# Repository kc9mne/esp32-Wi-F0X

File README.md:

# Wi-F0X

**A phone-configured 2 m fox-hunt beacon for the LilyGO T-Beam Supreme 144-148 MHz.**
By Paul Gariepy, KC9MNE — [kc9mne.com](https://kc9mne.com)

Wi-F0X turns a stock T-Beam Supreme (ESP32-S3 + SX1278, 2 m version) into a fox for
transmitter hunts and ARDF. You set it up from a phone over its own Wi-Fi: no PC, no
programming cable, no app. It has been used at a real hunt alongside Byonics MicroFox 50s.

### Demo

https://github.com/user-attachments/assets/96026c00-8a75-42aa-9971-1123c974c956

The prototype on the bench sending a voice clip and tracking tones, received on a handheld.
[Watch on YouTube](https://youtu.be/PTlThZ83Uh0) (41 s), or
[download the MP4](https://github.com/kc9mne/esp32-Wi-F0X/raw/main/media/wi-f0x-demo-720p.mp4) (8 MB).

## Features

- **Beacon cycle:** tracking tone, optional Morse message, then `DE <call> FOX <n>` in CW.
- **Tracking modes:** steady tone, warble, repeating ARDF MO pattern (MOE, MOI, MOS, MOH,
  MO5 for fox 1-5), and a **MicroFox 50 sequence** mode that matches the MF-50's tones and
  timing so Wi-F0X can join an existing MF-50 rotation.
- **Voice clips:** upload audio from the phone (converted in the browser to 8 kHz mono WAV)
  and play one clip per cycle, true FM. Good for jokes, taunts, or announcements.
- **Phone control page:** frequency, power, tone length, interval, start delay, run limit,
  pitch, Morse speed, auto start, and start/stop/test buttons.
- **OLED status:** a KC9MNE Wi-F0X boot screen, then fox ID and call, frequency and power, beacon state with countdown,
  battery percent and estimated runtime, Wi-Fi name and password, and a Wi-Fi QR code.
- **Settings survive power-off** (stored in the ESP32's flash).
- **Power:** 2-10 dBm selectable. The CPU idles at 80 MHz and only steps up for voice.

## Hardware

- LilyGO **T-Beam Supreme, 144-148 MHz** version (SX1278). The 433/868/915 MHz versions
  will not work on 2 m.
- An 18650 cell (tested with a Samsung INR18650-35E).
- A 2 m antenna on the SMA. **Never transmit without an antenna.**
- Optional: a microSD card (FAT32) for voice clips.

### Enclosure

A clear tube with rubber end caps makes a see-through, water-resistant fox: you can read the
OLED without opening it, and the antenna comes out through one cap.

- **Tube:** [MECCANIXITY rigid clear polycarbonate tube](https://www.amazon.com/dp/B0BKQCXM6C),
  1.5 in (37.6 mm) ID, 1.6 in (40 mm) OD, 9.6 in (245 mm) long. One tube is enough for two foxes.
- **End caps:** [standard 1.5 in rubber end caps](https://www.amazon.com/dp/B07RGMFH9F), two per fox.

Cut the tube in half (about 4.8 in each) so the T-Beam (with its 18650) slides in, fit a cap on each end, and
pass the antenna through a hole in one cap. Pull a cap off to reach the power switch.

## Build and flash

Install [PlatformIO](https://platformio.org/), plug the T-Beam in over USB-C, then:

```bash
pio run -t upload
```

The first upload may need download mode: hold BOOT, tap RESET, release BOOT. After that
the firmware can put itself into download mode: send `b` over the USB serial port at
115200 baud, upload, then clear the force-download flag so it boots normally:

```bash
esptool.py --before no_reset --after hard_reset write_mem 0x6000812C 0 0xFFFFFFFF
```

Other serial commands: `t` sends one test cycle, `r` restarts, `h` runs a web self-test.

## Using it

1. Power on. The OLED shows the Wi-F0X boot screen, then the status screen.
2. Wi-Fi is on for 5 minutes after boot. Press **BOOT** to turn it on again later.
   Until a phone joins, the OLED alternates between the status screen and a **QR code**:
   point your phone camera at it to join the fox's network. The network name (`FOX-xxxx`)
   and password are shown beside the code for typing in by hand. Each fox makes its own
   random password on first boot (two letters and six digits, e.g. `kc482913`) and keeps it.
3. Open `http://192.168.4.1` on the phone.
4. Open **Settings**, enter **your callsign**, fox number, frequency and timing, and save.
   The callsign starts as the placeholder `F0X-01`: change it to yours before you transmit.
5. Press **Test** to send one cycle, then **Start**. With a start delay set, the fox waits
   before its first transmission (handy for MF-50-style sequencing).
6. For voice, open **Audio** and upload clips from your phone.

## How the audio works

- **Tones and Morse** use RadioLib's `AFSKClient`, toggling the SX1278's DIO2 data pin while
  the radio is in direct FSK transmit mode.
- **Voice** is true FM done in software: the SX1278's FastHop mode lets the frequency change
  while transmitting, so the ESP32 writes a new carrier frequency over SPI 8,000 times a
  second, offset by each audio sample (up to ±4 kHz, in 61 Hz steps). A second task reads
  the SD card into a double buffer so the card never interrupts the audio. See `playClip()`
  in `src/main.cpp`.

## Rules and safety

- You need an amateur radio licence to transmit on 2 m, and the fox must identify with
  **your** callsign. Wi-F0X sends the CW ID every cycle.
- Power is capped at 10 dBm in the firmware. The T-Beam's harmonics have not been measured;
  check yours with a spectrum analyser or service monitor before raising power or running
  long hunts.
- US rules don't allow LoRa on 2 m; Wi-F0X uses only FM/FSK tones and voice.

## Custom board (experimental)

`hardware/` holds a dedicated, smaller Wi-F0X board in KiCad 9: ESP32-S3, SX1278 at
+14 dBm, TP4056 charger and an 18650 on the back, sized to fit a 37.6 mm clear tube. It is
fully routed with JLCPCB order files, but **has not been built or tested**, and at small
quantities it costs more than a T-Beam. See [hardware/README.md](hardware/README.md).

## License

MIT — see [LICENSE](LICENSE). If you build on Wi-F0X, please keep the credit to KC9MNE.

73 de KC9MNE

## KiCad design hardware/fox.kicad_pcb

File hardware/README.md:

# 2 m fox board: ESP32-S3 + SX1278

A dedicated board to replace the T-Beam Supreme: same firmware features (phone setup over
Wi-Fi, SD voice clips, MO patterns, Morse ID), 25 mW on 144–148 MHz, one 18650 cell,
target cost about $20 assembled at JLCPCB.

## Files

| File | What it is |
|---|---|
| `gen_schematic.py` | **Source of truth.** Every part and every connection. Edit this, then rerun it. |
| `fox.kicad_sch` | Generated schematic. Parts are connected by net labels on each pin, not drawn wires. |
| `fox.kicad_sym`, `sym-lib-table` | TP4056, FS8205A and TCXO symbols, which the stock KiCad libraries lack. |
| `fox.pdf`, `fox.net` | Exported schematic and netlist. |
| `fox_bom_jlc.csv` | JLCPCB assembly BOM (Comment, Designator, Footprint, LCSC Part #), one row per LCSC number. The OLED header J3 and the edge SMA J2 (C496550, clamps both sides of the edge) are left off and soldered by hand. |
| `check_netlist.py` | Confirms KiCad's netlist matches the script, pin by pin. |
| `rf_calc.py` | Matching-network and low-pass filter calculations quoted below. |
| `gen_board.py`, `autoroute.py`, `fox.kicad_pcb` | Board generator and router (KiCad's Python), and the routed board. |
| `silk.py` | Places reference labels clear of pads, vias and each other (autoroute.py runs it). |
| `fix_footprints.py`, `lib/`, `fp-lib-table` | LCSC footprints and 3D models, pads fixed to match the schematic. |
| `renders/` | 3D renders of the board. |
| `sexp.py` | Small KiCad file reader/writer used by the scripts. |

Regenerate and check:

```
python gen_schematic.py
kicad-cli sch erc fox.kicad_sch
kicad-cli sch export netlist --format kicadsexpr -o fox.net fox.kicad_sch
python check_netlist.py
```

Current state: ERC 0 violations; netlist check 83 nets, 265 pins, 0 problems.

## Blocks

**Power.** USB-C (5.1 k CC pull-downs, USBLC6 ESD) feeds a TP4056 charging the cell at
500 mA (R3 = 2.4 k). DW01A + FS8205A protect the unprotected Samsung 35E against
over-discharge (about 2.4 V), overcharge and short circuit. The slide switch sits after the
charger, so the cell charges with the fox switched off. An ME6211 LDO makes 3.3 V.
Below about 3.4 V the 3.3 V rail starts to sag; the firmware already stops transmitting at
3.3 V.

**Sensing.** VSYS/2 on GPIO 6 for battery voltage (replaces the AXP2101 readings).
VBUS/2 on GPIO 16 to tell when USB is plugged in. Charge state is on the red/green LEDs.

**ESP32-S3-WROOM-1-N8.** Radio, SD and OLED use the same GPIOs as the T-Beam Supreme, so
those parts of the firmware carry over unchanged:

| Function | GPIO |
|---|---|
| Radio SCK / MISO / MOSI / NSS | 12 / 13 / 11 / 10 |
| Radio RESET / DIO0 / DIO1 / DIO2 | 5 / 2 / 1 / 4 |
| SD SCK / MISO / MOSI / CS | 36 / 37 / 35 / 47 |
| OLED SDA / SCL | 17 / 18 |
| Battery sense / USB sense / status LED | 6 / 16 / 7 |
| BOOT button | 0 |

GPIO 35–37 are free only because the N8 module has no octal PSRAM; don't substitute an
N8R8 or N16R8 module.

**Radio.** SX1278 with an Epson TG2520SMN 32 MHz clipped-sine TCXO (±0.5 ppm, about
±75 Hz at 146 MHz) AC-coupled into XTA through 10 nF, XTB open. TCXO pin 1 is grounded:
Epson says it must be open or grounded. The firmware must set `RegTcxo` (0x4B) bit 4
before starting the radio, and switch output from PA_BOOST to the RFO pin.

**OLED firmware change.** The T-Beam has a 1.3 in SH1106; 0.96 in modules are usually
SSD1306, so the U8g2 setup call changes from `sh1106` to `ssd1306` (otherwise the image
is shifted by 2 pixels). Read upright, the module's header is at the top of the image,
which here is the ESP32 end. If the fox hangs cap end up, use `U8G2_R2` to turn the image.

The FS8205A is the SOT-23-6 version (the TSSOP-8 one is out of stock). Its pinout is from
the Tech Public datasheet: 1 S1, 2 D, 3 S2, 4 G2, 5 D, 6 G1.

## RF network

Semtech AN1200.19 Figure 6, the single-path RFO_LF/RFI_LF design: transmit and receive
share one port, so no RF switch is needed. Semtech warns against combining PA_BOOST with
RFI this way, which is why output is the RFO pin at up to +14 dBm (25 mW) rather than
PA_BOOST at +17 dBm.

Every value is Semtech's 169 MHz BOM scaled by 169/146 and rounded to a standard value:

| Semtech | 169 MHz | This board | 146 MHz | Role |
|---|---|---|---|---|
| Lp | 100 nH | L1 | 120 nH | PA bias feed from VR_PA |
| Cd | 220 pF | C20 | 270 pF | VR_PA decoupling (+ C21 10 nF) |
| C1 | 15 pF | C22 | 18 pF | shunt at the RF pin |
| C10 | 5.6 pF | C23 | 6.8 pF | RX branch |
| L0 | 82 nH | L2 | 91 nH | RX branch to ground |
| L1 | 56 nH | L3 | 68 nH | series match |
| Cc | 220 pF | C24 | 270 pF | DC block |
| C2 / C3 | 33 pF | C25 / C26 | 39 pF | low-pass |
| L2 | 47 nH | L4 | 56 nH | low-pass |
| L3 | 33 nH | L5 | 39 nH | low-pass |
| C4 | 8.2 pF | C27 | 9.1 pF | low-pass |

Calculated with ideal parts (`rf_calc.py`):

- Impedance the network presents to the RF pin: 47.4 − j30.6 Ω at 146 MHz, against
  52.7 − j28.0 Ω for Semtech's own values at 169 MHz. Semtech's table gives the optimum as
  47.8 + j28.9, the conjugate, so the scaled network lands in the same place.
- Across 144–148 MHz it moves only from 51 to 44 Ω real, so one build covers the band.

After C27 there is a 0 Ω link (R19) and a second 5-pole 0.1 dB Chebyshev low-pass
(22 pF – 68 nH – 39 pF – 68 nH – 22 pF, cutoff about 170 MHz) in front of the SMA:

| | 146 MHz | 2nd (292) | 3rd (438) | 4th (584) |
|---|---|---|---|---|
| Semtech low-pass | 0.34 dB | 20.9 dB | 39.7 dB | 52.9 dB |
| Both filters | 0.4 dB | 50.4 dB | 88.9 dB | 115 dB |

That is filter attenuation only, on top of whatever the chip's own harmonics are.
§97.307(e) asks for spurious emissions at least 40 dB below the carrier on 2 m at this
power. Real inductors lose some of that at high harmonics because of self-resonance.

## Tuning the first board

The scaled values are a starting point: the chip's port impedance doesn't scale exactly
with frequency, and board layout adds its own reactance. Plan on adjusting part values.

1. Lift R19 and sweep the second filter alone on the NanoVNA (SMA to a probe at R19's pad).
   Expect under 0.5 dB loss at 146 MHz and a return loss better than 15 dB.
2. Refit R19. With the radio transmitting a carrier at +14 dBm, read output power and
   harmonics on the service monitor through an attenuator.
3. If power is low, adjust C22 (shunt) and L3 (series) first; they set the match.
4. Check receive later, when the control link is built.

## Cost

LCSC prices at about 50 pieces, checked 2026-11-02:

| | Per board |
|---|---|
| ESP32-S3-WROOM-1-N8 | $3.83 |
| SX1278IMLTRT | $3.52 |
| TCXO, charger, protection, LDO, ESD | about $0.75 |
| USB-C, microSD, SMA, 18650 holder, switches | about $0.90 |
| RF inductors and capacitors (Murata, ±2 %) | about $0.60 |
| Other passives and LEDs | about $0.20 |
| **Parts** | **about $9.80** |

JLCPCB adds a one-off loading fee per extended part type (about $3 each, roughly 27 types
here), plus setup, stencil and the bare PCBs. Spread over 10 boards that is roughly $10 more
each, so about $20 a board; over 30 boards about $14. Those fees are from memory, so check
JLC's quote. The OLED (about $2–3) and the cell are extra.

Stock to watch: the ESP32-S3-WROOM-1-N8 had only 395 at LCSC and 1215 at JLC.

## Board

`fox.kicad_pcb` is built in two steps, both run with KiCad's own Python
(`"C:\Program Files\KiCad\9.0\bin\python.exe"`):

1. `gen_board.py`: outline, every part placed with its nets, ground pours, and the
   hand-routed parts (RF section, USB-C escape, the radio's 3.3 V pin).
2. `autoroute.py`: first ties every ground pad in the digital half (x > 48) together with
   0.2 mm ground traces, so later signal traces can't fence a ground pad off on both
   layers; then routes everything else, adds ground stitching vias (kept 0.3 mm
   hole-to-hole from other holes), joins any cut-off pieces of ground pour, fills the
   pours and places the labels (`silk.py`). Takes several minutes.

Labels are 0.8 mm text (1 mm on big parts), JLCPCB's minimum. Where there is no clear spot
next to a part (the tight RF and radio area, and U1 under its own module), the label goes
on the Fab layer only: it shows on the assembly drawing but isn't printed.

**It is fully routed.** Rules check: 0 errors, 0 unconnected, and the board matches the
schematic exactly (`kicad-cli pcb drc --schematic-parity`). Clearance is 0.15 mm, tracks
0.2 mm (power 0.3–0.6 mm), vias 0.6/0.3 mm (0.5/0.3 at the USB-C), all within JLCPCB's
standard 2-layer process.

The autorouter is a simple maze router written for this board, so its traces wander more
than a person's would. Electrically that doesn't matter at these speeds (SPI, I2C, USB
full-speed), but tidy anything you care about in the PCB editor. It keeps the bottom layer
unbroken under the RF chain and stays out of the ESP32 antenna keepout.

**RF routing (done, in `ROUTES` in `gen_board.py`).** The matching parts sit in a line
right at the SX1278's RF pin (pin 28), series parts on the line and each shunt capacitor
hanging below it with its own ground via. The long run is the 1.0 mm line from the SMA to
the filter, with stitching vias both sides and vias in the SMA's ground legs. Also routed:
the RX branch to RFI_LF (pin 1), the VR_PA bias feed (L1, C20, C21), the TCXO through C19
to XTA, and the radio's ground pins into its exposed pad. At 146 MHz the longest trace is
about 0.02 wavelength, so keeping it short over solid ground matters more than its exact
impedance.

C16 and C17 (VR_ANA, VR_DIG decoupling) sit straight out from pins 2 and 4, with L2
moved up beside C23 to make room.

**USB-C (hand-routed).** The receptacle's pins are 0.5 mm apart and D+ and D- each appear
twice (A and B rows, for a reversible plug). D+ joins on top, threading between two D-
vias; D- joins on the bottom. CC1 and CC2 run straight out to their 5.1 k resistors.

- **34 × 110 mm, 2 layers.** All parts on top except the 18650 holder, which is on the
  bottom. Its two pins (x = 10 and 80) and centre peg hole come up through the board.
- **Cap end (x = 0):** SMA, slide switch and USB-C, reachable with the cap off.
- **Far end:** the ESP32 module, its Wi-Fi antenna flush with the board end and past the
  end of the battery. The footprint carries its own no-copper zone in front of the antenna.
- **RF chain** along the top edge from the SMA to the SX1278, in schematic order.
- **Tube fit (37.6 mm inside):** mount the board with its top face about 4–5 mm above the
  tube's centre line, so the holder (18.3 mm deep, 20.95 mm wide) and cell clear below.
  That leaves about 8.5 mm above the board, so the OLED must be mounted low (pins soldered
  straight through, short spacer), not on a normal female header. A 1.3 in OLED won't fit.
  The SMA is 10 mm off-centre, so the antenna hole in the cap is too.
- **Slide switch:** its lever sticks 1.5 mm past the cap-end edge (the part's full lever
  length), so it can be switched with the cap off.
- **microSD:** the slot opens at the top long edge (y = 0), so a card goes in and out with
  the board slid out of the tube.
- **OLED (J3):** a 0.96 in I2C module (27.3 × 27.8 mm), landscape across the board like the
  T-Beam's display. Its header runs across the board on the centre line at x = 75.4, and the
  module reaches back toward the cap end over the SD socket and small parts (x ≈ 49–77).
  Nothing under it needs pressing or seeing. RESET and BOOT (SW2, SW3) sit beside it at
  x = 45, the status LED beyond its header end.
- **No UART header.** Flashing and the serial console go over the USB-C port (the
  ESP32-S3's built-in USB-Serial-JTAG). A pin header near the long edge would also hit
  the tube wall.

Footprints for the holder, SMA, microSD, slide switch and tact switches come from LCSC's
EasyEDA library via `easyeda2kicad` (`lib/fox_lcsc.pretty`, with 3D models).
`fix_footprints.py` copies them to `lib/fox.pretty`, renumbering pads to match the
schematic (battery + and −, SMA centre pin, SD shell, tact switch pairs; each checked
against the datasheet) and making locating holes non-plated.

Renders are in `renders/` (`kicad-cli pcb render`). The SMA's downloaded 3D model was
backwards; `fix_footprints.py` corrects it so the barrel sits off the cap end with the board
between its legs (the footprint itself was always right). The USB-C connector has no 3D model in
this KiCad install, so it shows as bare pads.

### Ordering from JLCPCB

Install the **JLCPCB Tools** plugin (Plugin and Content Manager). It writes the Gerbers,
drill file, BOM and placement file; the LCSC numbers come from the schematic. The holder
is through-hole on the bottom: solder its two pins by hand from the top.

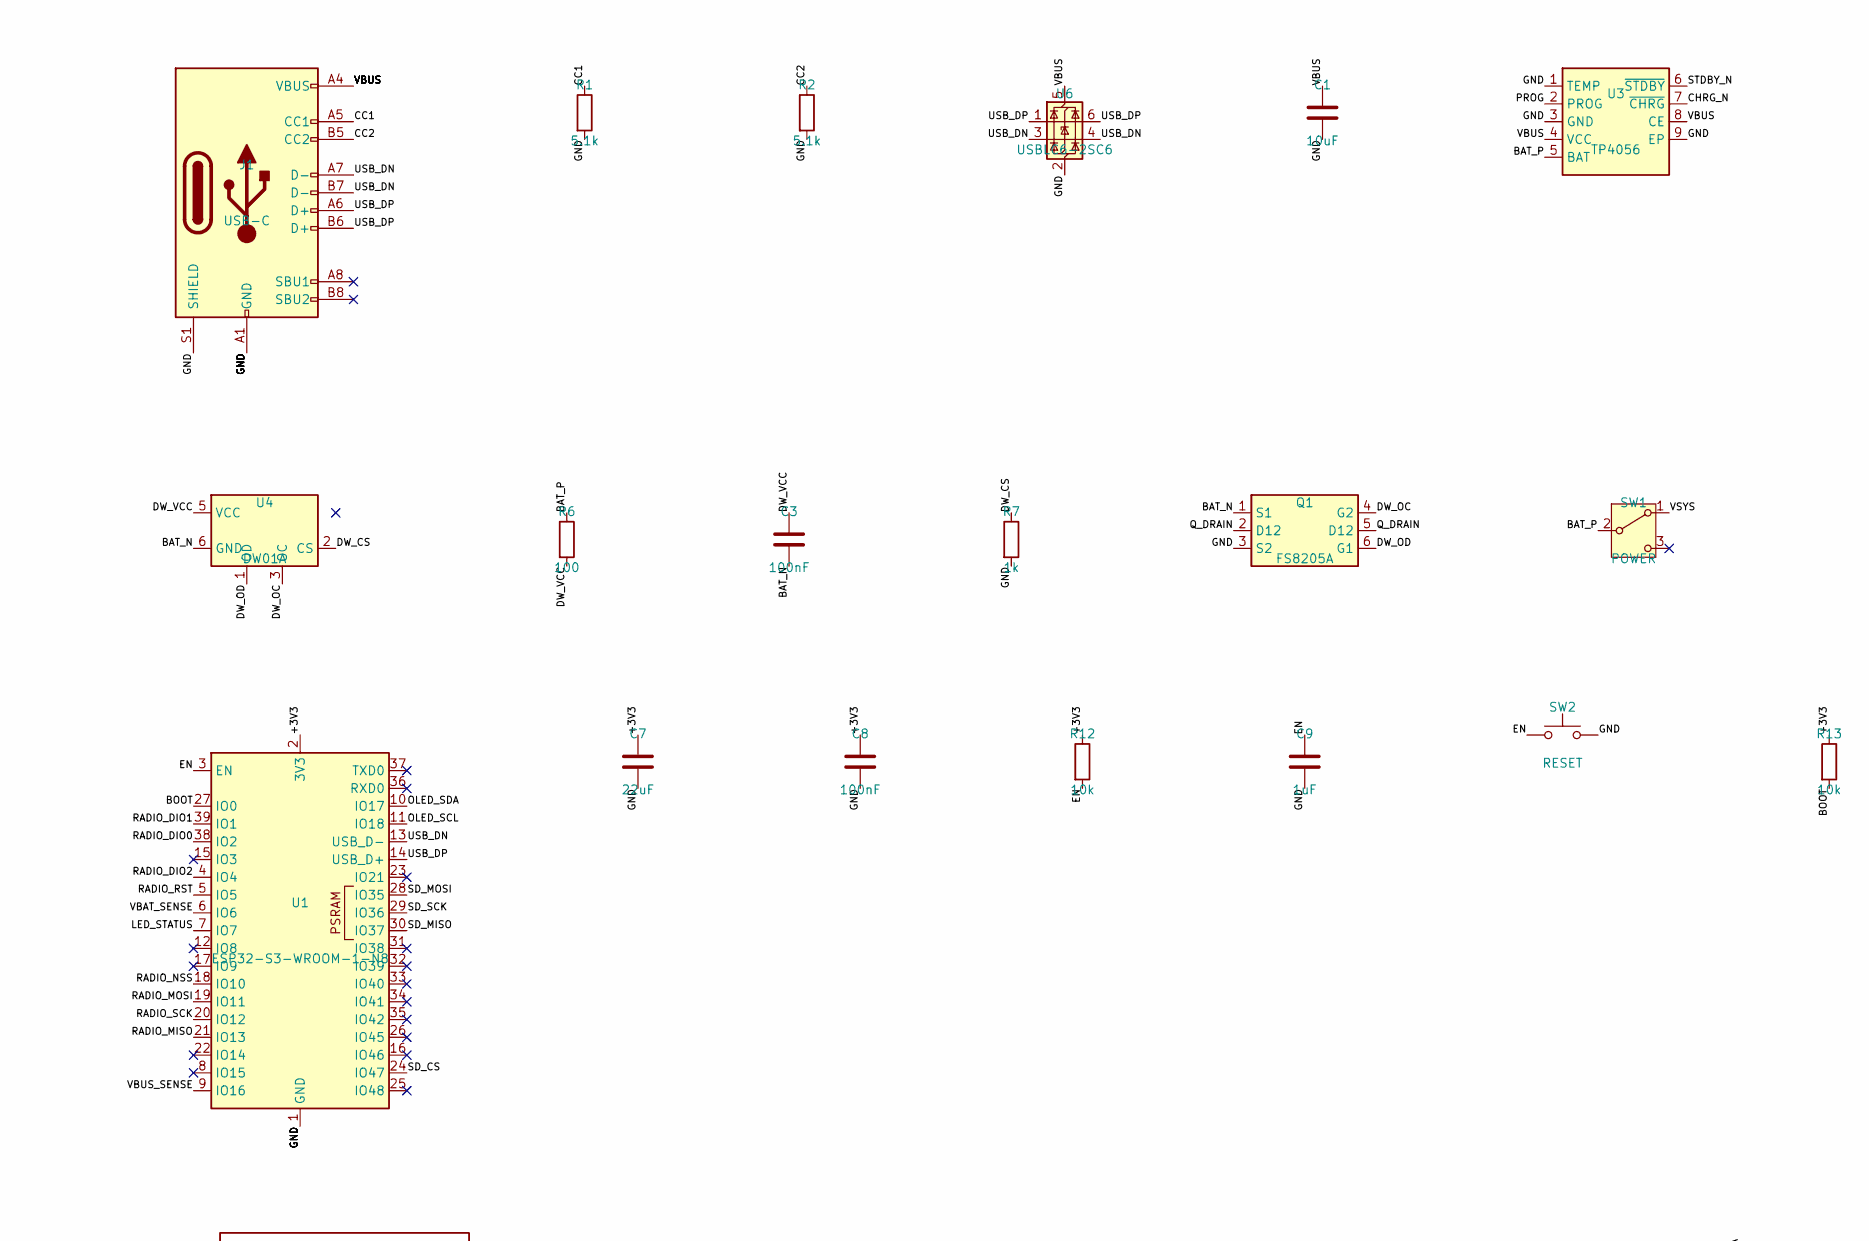
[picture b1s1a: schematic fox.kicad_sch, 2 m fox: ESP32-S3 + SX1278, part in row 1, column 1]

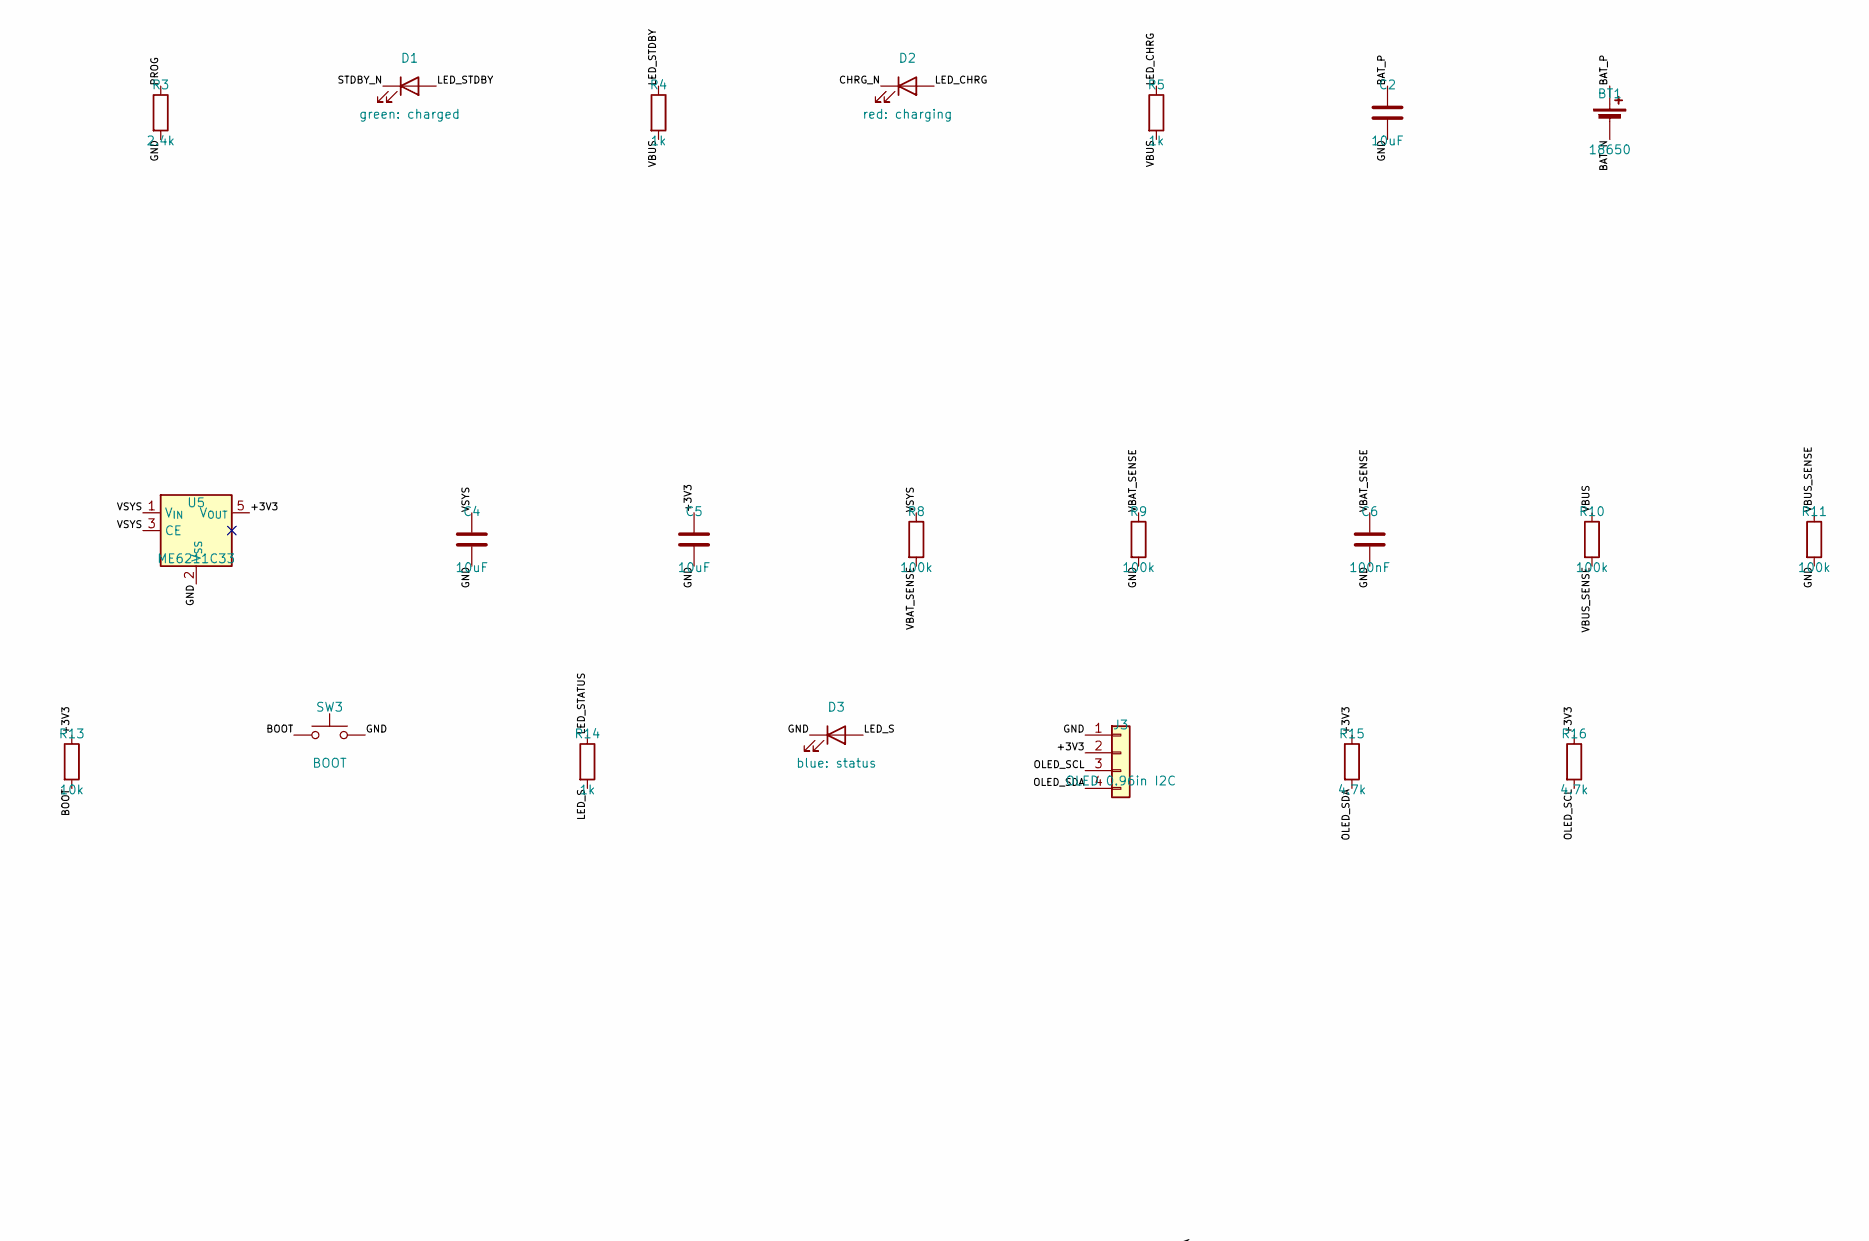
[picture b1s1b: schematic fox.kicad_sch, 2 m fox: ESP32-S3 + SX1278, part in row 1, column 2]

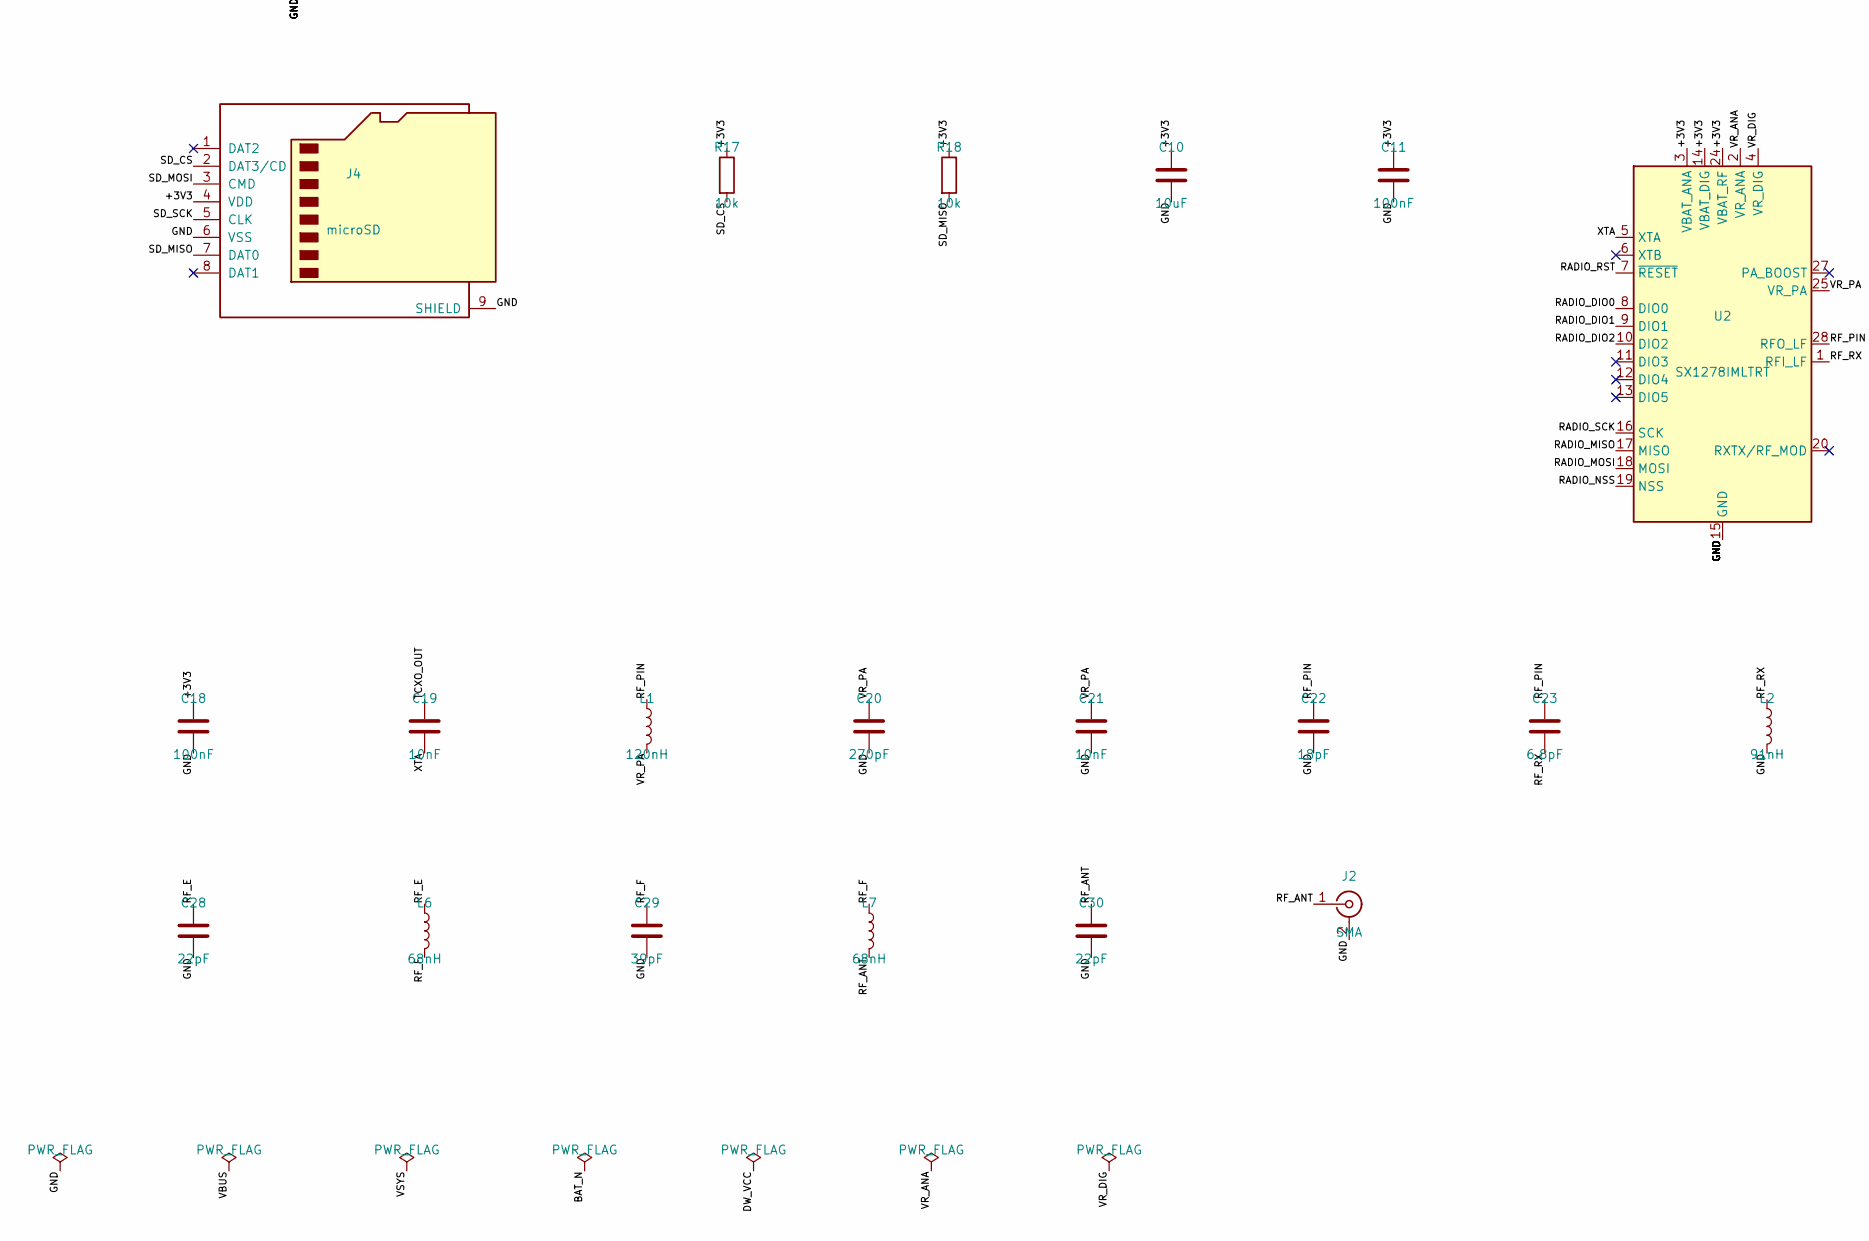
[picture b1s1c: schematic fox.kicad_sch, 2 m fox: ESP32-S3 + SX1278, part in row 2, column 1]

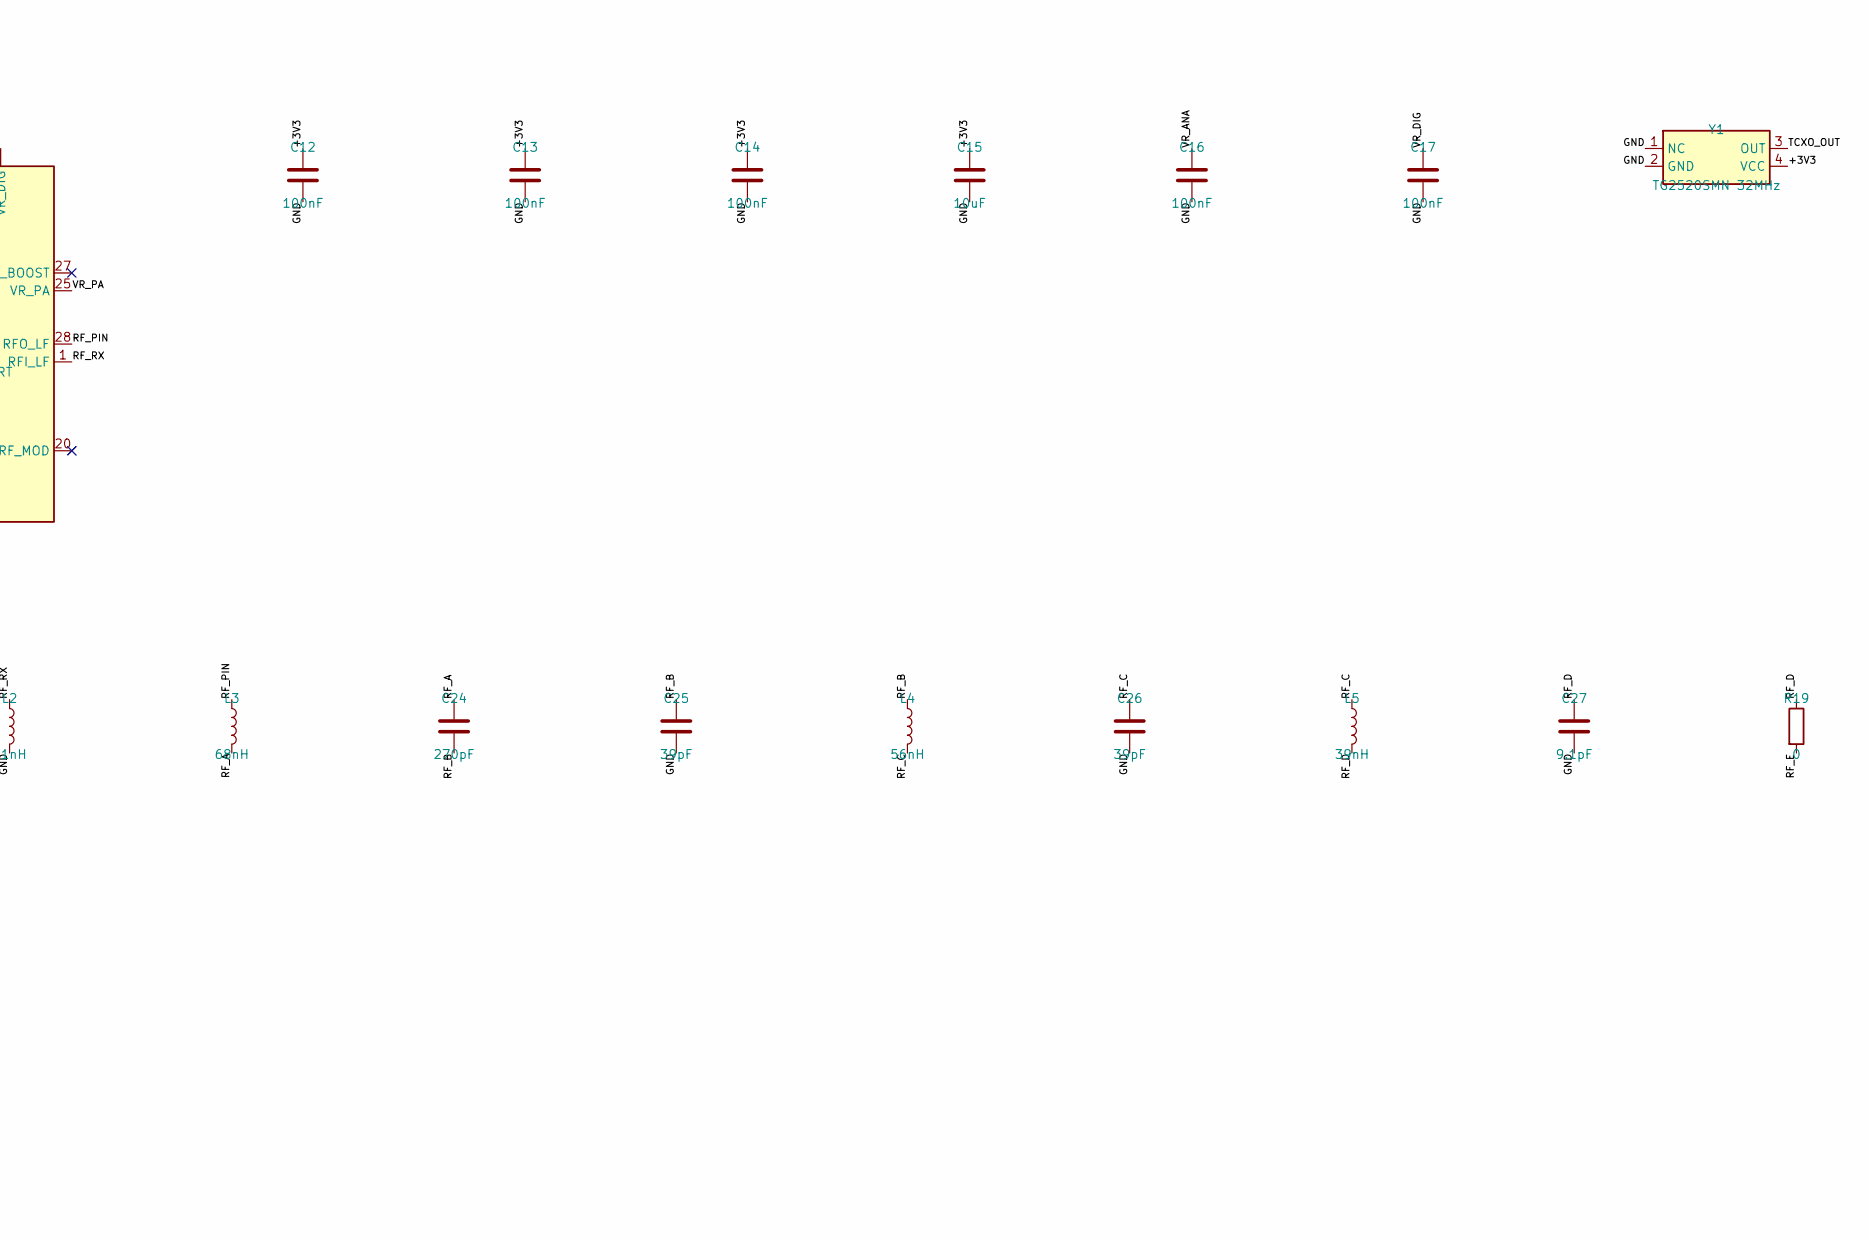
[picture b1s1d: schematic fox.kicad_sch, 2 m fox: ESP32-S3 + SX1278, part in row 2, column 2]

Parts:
BT1: 18650; BAT-TH_BH-18650-A1AJ005; LCSC C49118395
C1, C2, C4, C5, C10, C15: 10uF; C_0805_2012Metric; LCSC C15850
C3, C6, C8, C11, C12, C13, C14, C16, C17, C18: 100nF; C_0402_1005Metric; LCSC C1525
C7: 22uF; C_0805_2012Metric; LCSC C45783
C9: 1uF; C_0402_1005Metric; LCSC C52923
C19, C21: 10nF; C_0402_1005Metric; LCSC C15195
C20, C24: 270pF; C_0402_1005Metric; LCSC C161546
C22: 18pF; C_0402_1005Metric; LCSC C1549
C23: 6.8pF; C_0402_1005Metric; LCSC C1576
C25, C26, C29: 39pF; C_0402_1005Metric; LCSC C1864552
C27: 9.1pF; C_0402_1005Metric; LCSC C64366
C28, C30: 22pF; C_0402_1005Metric; LCSC C1555
D1: green: charged; LED_0603_1608Metric; LCSC C965804
D2: red: charging; LED_0603_1608Metric; LCSC C2286
D3: blue: status; LED_0603_1608Metric; LCSC C965807
J1: USB-C; USB_C_Receptacle_HRO_TYPE-C-31-M-12; LCSC C165948
J2: SMA; SMA-SMD_BWSMA-KE-P001; LCSC C496550
J3: OLED 0.96in I2C; PinHeader_1x04_P2.54mm_Vertical
J4: microSD; TF-SMD_TF-01A; LCSC C91145
L1: 120nH; L_0402_1005Metric; LCSC C113123
L2: 91nH; L_0402_1005Metric; LCSC C113121
L3, L6, L7: 68nH; L_0402_1005Metric; LCSC C108965
L4: 56nH; L_0402_1005Metric; LCSC C167482
L5: 39nH; L_0402_1005Metric; LCSC C98059
Q1: FS8205A; SOT-23-6; LCSC C2830320
R1, R2: 5.1k; R_0402_1005Metric; LCSC C25905
R3: 2.4k; R_0402_1005Metric; LCSC C25882
R4, R5, R7, R14: 1k; R_0402_1005Metric; LCSC C11702
R6: 100; R_0402_1005Metric; LCSC C25076
R8, R9, R10, R11: 100k; R_0402_1005Metric; LCSC C25741
R12, R13, R17, R18: 10k; R_0402_1005Metric; LCSC C25744
R15, R16: 4.7k; R_0402_1005Metric; LCSC C25900
R19: 0; R_0402_1005Metric; LCSC C17168
SW1: POWER; SW-TH_MSK12C02; LCSC C431540
SW2: RESET; SW-SMD_4P-L5.1-W5.1-P3.70-LS6.5-TL_H1.5; LCSC C318884
SW3: BOOT; SW-SMD_4P-L5.1-W5.1-P3.70-LS6.5-TL_H1.5; LCSC C318884
U1: ESP32-S3-WROOM-1-N8; ESP32-S3-WROOM-1; LCSC C2913198
U2: SX1278IMLTRT; QFN-28-1EP_6x6mm_P0.65mm_EP4.8x4.8mm; LCSC C67678
U3: TP4056; SOIC-8-1EP_3.9x4.9mm_P1.27mm_EP2.29x3mm; LCSC C16581
U4: DW01A; SOT-23-6; LCSC C351410
U5: ME6211C33; SOT-23-5; LCSC C82942
U6: USBLC6-2SC6; SOT-23-6; LCSC C7519
Y1: TG2520SMN 32MHz; Oscillator_SMD_SeikoEpson_TG2520SMN-xxx-xxxxxx-4Pin_2.5x2.0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; LCSC C3007516

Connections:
/+3V3: C5.1, C7.1, C8.1, C10.1, C11.1, C12.1, C13.1, C14.1, C15.1, C18.1, J3.2, J4.4 (VDD), R12.1, R13.1, R15.1, R16.1, R17.1, R18.1, U1.2 (3V3), U2.3 (VBAT_ANA), U2.14 (VBAT_DIG), U2.24 (VBAT_RF), U5.5 (V_{OUT}), Y1.4 (VCC)
/BAT_N: BT1.2 (-), C3.2, Q1.1 (S1), U4.6 (GND)
/BAT_P: BT1.1 (+), C2.1, R6.1, SW1.2 (B), U3.5 (BAT)
/BOOT: R13.2, SW3.1, U1.27 (IO0)
/CC1: J1.A5 (CC1), R1.1
/CC2: J1.B5 (CC2), R2.1
/CHRG_N: D2.1 (K), U3.7 (~CHRG)
/DW_CS: R7.1, U4.2 (CS)
/DW_OC: Q1.4 (G2), U4.3 (OC)
/DW_OD: Q1.6 (G1), U4.1 (OD)
/DW_VCC: C3.1, R6.2, U4.5 (VCC)
/EN: C9.1, R12.2, SW2.1, U1.3 (EN)
/GND: C1.2, C2.2, C4.2, C5.2, C6.2, C7.2, C8.2, C9.2, C10.2, C11.2, C12.2, C13.2, C14.2, C15.2, C16.2, C17.2, C18.2, C20.2, C21.2, C22.2, C25.2, C26.2, C27.2, C28.2, C29.2, C30.2, D3.1 (K), J1.A1 (GND), J1.A12 (GND), J1.B1 (GND), J1.B12 (GND), J1.S1 (SHIELD), J2.2 (Ext), J3.1, J4.6 (VSS), J4.9 (SHIELD), L2.2, Q1.3 (S2), R1.2, R2.2, R3.2, R7.2, R9.2, R11.2, SW2.2, SW3.2, U1.1 (GND), U1.40 (GND), U1.41 (GND), U2.15 (GND), U2.21 (GND), U2.22 (GND), U2.23 (GND), U2.26 (GND), U2.29 (GND), U3.1 (TEMP), U3.3 (GND), U3.9 (EP), U5.2 (V_{SS}), U6.2 (GND), Y1.1 (NC), Y1.2 (GND)
/LED_CHRG: D2.2 (A), R5.1
/LED_S: D3.2 (A), R14.2
/LED_STATUS: R14.1, U1.7 (IO7)
/LED_STDBY: D1.2 (A), R4.1
/OLED_SCL: J3.3, R16.2, U1.11 (IO18)
/OLED_SDA: J3.4, R15.2, U1.10 (IO17)
/PROG: R3.1, U3.2 (PROG)
/Q_DRAIN: Q1.2 (D12), Q1.5 (D12)
/RADIO_DIO0: U1.38 (IO2), U2.8 (DIO0)
/RADIO_DIO1: U1.39 (IO1), U2.9 (DIO1)
/RADIO_DIO2: U1.4 (IO4), U2.10 (DIO2)
/RADIO_MISO: U1.21 (IO13), U2.17 (MISO)
/RADIO_MOSI: U1.19 (IO11), U2.18 (MOSI)
/RADIO_NSS: U1.18 (IO10), U2.19 (NSS)
/RADIO_RST: U1.5 (IO5), U2.7 (~RESET)
/RADIO_SCK: U1.20 (IO12), U2.16 (SCK)
/RF_A: C24.1, L3.2
/RF_ANT: C30.1, J2.1 (In), L7.2
/RF_B: C24.2, C25.1, L4.1
/RF_C: C26.1, L4.2, L5.1
/RF_D: C27.1, L5.2, R19.1
/RF_E: C28.1, L6.1, R19.2
/RF_F: C29.1, L6.2, L7.1
/RF_PIN: C22.1, C23.1, L1.1, L3.1, U2.28 (RFO_LF)
/RF_RX: C23.2, L2.1, U2.1 (RFI_LF)
/SD_CS: J4.2 (DAT3/CD), R17.2, U1.24 (IO47)
/SD_MISO: J4.7 (DAT0), R18.2, U1.30 (IO37)
/SD_MOSI: J4.3 (CMD), U1.28 (IO35)
/SD_SCK: J4.5 (CLK), U1.29 (IO36)
/STDBY_N: D1.1 (K), U3.6 (~STDBY)
/TCXO_OUT: C19.1, Y1.3 (OUT)
/USB_DN: J1.A7 (D-), J1.B7 (D-), U1.13 (USB_D-), U6.3 (I/O2), U6.4 (I/O2)
/USB_DP: J1.A6 (D+), J1.B6 (D+), U1.14 (USB_D+), U6.1 (I/O1), U6.6 (I/O1)
/VBAT_SENSE: C6.1, R8.2, R9.1, U1.6 (IO6)
/VBUS: C1.1, J1.A4 (VBUS), J1.A9 (VBUS), J1.B4 (VBUS), J1.B9 (VBUS), R4.2, R5.2, R10.1, U3.4 (VCC), U3.8 (CE), U6.5 (VBUS)
/VBUS_SENSE: R10.2, R11.1, U1.9 (IO16)
/VR_ANA: C16.1, U2.2 (VR_ANA)
/VR_DIG: C17.1, U2.4 (VR_DIG)
/VR_PA: C20.1, C21.1, L1.2, U2.25 (VR_PA)
/VSYS: C4.1, R8.1, SW1.1 (A), U5.1 (V_{IN}), U5.3 (CE)
/XTA: C19.2, U2.5 (XTA)

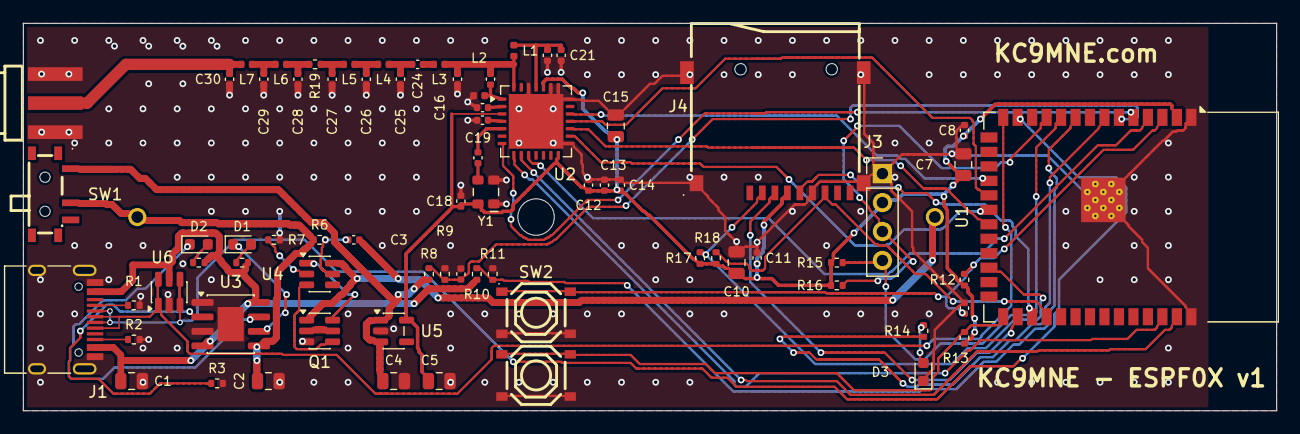
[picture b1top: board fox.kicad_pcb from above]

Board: 2 copper layers, 110.0 x 34.0 mm, 75 parts (1 on the bottom side), 54 nets.

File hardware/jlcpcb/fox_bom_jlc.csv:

Comment,Designator,Footprint,LCSC Part #
"18650","BT1","BAT-TH_BH-18650-A1AJ005",C49118395
"10uF","C1,C2,C4,C5,C10,C15","C_0805_2012Metric",C15850
"10nF","C19,C21","C_0402_1005Metric",C15195
"270pF","C20,C24","C_0402_1005Metric",C161546
"18pF","C22","C_0402_1005Metric",C1549
"6.8pF","C23","C_0402_1005Metric",C1576
"39pF","C25,C26,C29","C_0402_1005Metric",C1864552
"9.1pF","C27","C_0402_1005Metric",C64366
"22pF","C28,C30","C_0402_1005Metric",C1555
"100nF","C3,C6,C8,C11,C12,C13,C14,C16,C17,C18","C_0402_1005Metric",C1525
"22uF","C7","C_0805_2012Metric",C45783
"1uF","C9","C_0402_1005Metric",C52923
"green: charged","D1","LED_0603_1608Metric",C965804
"red: charging","D2","LED_0603_1608Metric",C2286
"blue: status","D3","LED_0603_1608Metric",C965807
"USB-C","J1","USB_C_Receptacle_HRO_TYPE-C-31-M-12",C165948
"microSD","J4","TF-SMD_TF-01A",C91145
"120nH","L1","L_0402_1005Metric",C113123
"91nH","L2","L_0402_1005Metric",C113121
"68nH","L3,L6,L7","L_0402_1005Metric",C108965
"56nH","L4","L_0402_1005Metric",C167482
"39nH","L5","L_0402_1005Metric",C98059
"FS8205A","Q1","SOT-23-6",C2830320
"5.1k","R1,R2","R_0402_1005Metric",C25905
"10k","R12,R13,R17,R18","R_0402_1005Metric",C25744
"4.7k","R15,R16","R_0402_1005Metric",C25900
"0","R19","R_0402_1005Metric",C17168
"2.4k","R3","R_0402_1005Metric",C25882
"1k","R4,R5,R7,R14","R_0402_1005Metric",C11702
"100","R6","R_0402_1005Metric",C25076
"100k","R8,R9,R10,R11","R_0402_1005Metric",C25741
"POWER","SW1","SW-TH_MSK12C02",C431540
"RESET/BOOT","SW2,SW3","SW-SMD_4P-L5.1-W5.1-P3.70-LS6.5-TL_H1.5",C318884
"ESP32-S3-WROOM-1-N8","U1","ESP32-S3-WROOM-1",C2913198
"SX1278IMLTRT","U2","QFN-28-1EP_6x6mm_P0.65mm_EP4.8x4.8mm",C67678
"TP4056","U3","SOIC-8-1EP_3.9x4.9mm_P1.27mm_EP2.29x3mm",C16581
"DW01A","U4","SOT-23-6",C351410
"ME6211C33","U5","SOT-23-5",C82942
"USBLC6-2SC6","U6","SOT-23-6",C7519
"TG2520SMN 32MHz","Y1","Oscillator_SMD_SeikoEpson_TG2520SMN-xxx-xxxxxx-4Pin_2.5x2.0mm",C3007516

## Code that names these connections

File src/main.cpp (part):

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#include <qrcode.h>

// Pin map from LilyGO's T-Beam Supreme 144-148 MHz hardware doc.
constexpr int PIN_OLED_SDA = 17;
constexpr int PIN_OLED_SCL = 18;
constexpr int PIN_PMU_SDA = 42;
constexpr int PIN_PMU_SCL = 41;
constexpr int PIN_RADIO_SCK = 12;
constexpr int PIN_RADIO_MISO = 13;
constexpr int PIN_RADIO_MOSI = 11;
constexpr int PIN_RADIO_CS = 10;
constexpr int PIN_RADIO_RST = 5;
constexpr int PIN_RADIO_DIO0 = 2;
constexpr int PIN_RADIO_DIO1 = 1;
constexpr int PIN_RADIO_DIO2 = 4;
constexpr int PIN_BOOT_BUTTON = 0;
constexpr int PIN_SD_SCK = 36;
constexpr int PIN_SD_MISO = 37;
constexpr int PIN_SD_MOSI = 35;
constexpr int PIN_SD_CS = 47;
constexpr int PIN_IMU_CS = 34;

// SX1278 FSK registers and frequency step for retuning during audio.
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XPowersAXP2101 pmu;
SPIClass radioSpi(FSPI);
SPIClass sdSpi(HSPI);
Module radioModule(PIN_RADIO_CS, PIN_RADIO_DIO0, PIN_RADIO_RST, PIN_RADIO_DIO1, radioSpi);
SX1278 radio = &radioModule;
AFSKClient audio(&radio, PIN_RADIO_DIO2);
MorseClient morse(&audio);
U8G2 display;
AsyncWebServer server(80);
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  Module *mod = &radioModule;
  radio.setFrequencyDeviation(AUDIO_FM_DEVIATION_KHZ);
  radio.transmitDirect();
  pinMode(PIN_RADIO_DIO2, OUTPUT);
  digitalWrite(PIN_RADIO_DIO2, LOW);
  uint8_t pllHop = mod->SPIreadRegister(REG_PLL_HOP);
  mod->SPIwriteRegister(REG_PLL_HOP, pllHop | FAST_HOP_ON);

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}

void setupDisplay() {
  Wire.begin(PIN_OLED_SDA, PIN_OLED_SCL);
  Wire.setTimeOut(20);
  for (uint8_t address : {0x3C, 0x3D}) {
    Wire.beginTransmission(address);
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// With format set, the library formats the card only if it has no valid FAT
// volume, so a readable card is never erased here.
void mountSd(bool format) {
  sdReadable = SD.begin(PIN_SD_CS, sdSpi, 4000000U, "/sd", 5, format);
  if (!sdReadable) {
    snprintf(sdInfo, sizeof(sdInfo), "not readable (no card, or not FAT)");
    Serial.printf("SD: %s\n", sdInfo);
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void setupSd() {
  pinMode(PIN_IMU_CS, OUTPUT);
  digitalWrite(PIN_IMU_CS, HIGH);
  sdSpi.begin(PIN_SD_SCK, PIN_SD_MISO, PIN_SD_MOSI, PIN_SD_CS);
  mountSd(false);
}

void setupRadio() {
  Settings current = currentSettings();
  radioSpi.begin(PIN_RADIO_SCK, PIN_RADIO_MISO, PIN_RADIO_MOSI, PIN_RADIO_CS);
  // 4.8 kbps, 5 kHz deviation, 125 kHz RX bandwidth, 16 bit preamble.
  radioState = radio.beginFSK(current.frequency, 4.8, 5.0, 125.0, current.power, 16, false);
  if (radioState == RADIOLIB_ERR_NONE) {
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
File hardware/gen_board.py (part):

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    "C28": (24.1, 4.9, 270), "R19": (25.6, 3.6, 180), "C27": (27.1, 4.9, 270), "L5": (28.6, 3.6, 180),
    "C26": (30.1, 4.9, 270), "L4": (31.6, 3.6, 180), "C25": (33.1, 4.9, 270), "C24": (34.6, 3.6, 180),
    "L3": (36.5, 3.6, 180),
    # RF pin node: shunt C22, RX branch C23 then L2 to ground, bias feed L1 up to VR_PA
    "C22": (38.1, 4.9, 270), "C23": (41.0, 4.9, 270), "L2": (40.0, 6.35, 180),
    # VR_ANA and VR_DIG decoupling, straight out from pins 2 and 4
    "C16": (40.3, 7.4, 180), "C17": (40.3, 8.5, 180),
    "L1": (43.05, 2.4, 90), "C20": (46.0, 2.8, 270), "C21": (47.2, 2.8, 270),
    "U2": (45.0, 8.6, 0),
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    ("/RF_B", RF_W, [("L4", "1"), ("C24", "2")]), ("/RF_B", RF_W, [(33.1, RF_Y), ("C25", "1")]),
    ("/RF_A", RF_W, [("C24", "1"), ("L3", "2")]),
    # RF pin node at (43.05, RF_Y): line from L3, shunt C22, RX cap C23, bias choke L1
    ("/RF_PIN", RF_W, [("L3", "1"), (43.05, RF_Y)]),
    ("/RF_PIN", RF_W, [(38.1, RF_Y), ("C22", "1")]),
    ("/RF_PIN", RF_W, [(41.0, RF_Y), ("C23", "1")]),
    ("/RF_PIN", SIG_W, [("L1", "1"), (43.05, RF_Y), ("U2", "28")]),
    # RX branch: C23 down to RFI_LF, L2 to ground
    ("/RF_RX", SIG_W, [("C23", "2"), (41.0, 6.35), ("U2", "1")]),
    ("/RF_RX", SIG_W, [("L2", "1"), (41.0, 6.35)]),
    # regulator decoupling
    ("/VR_ANA", SIG_W, [("U2", "2"), ("C16", "1")]),
    ("/VR_DIG", SIG_W, [("U2", "4"), ("C17", "1")]),
    # VR_PA: choke L1 to pin 25, decoupled by C20 and C21
    ("/VR_PA", SIG_W, [("L1", "2"), (45.0, 1.92), ("U2", "25")]),
    ("/VR_PA", SIG_W, [(45.0, 1.92), (47.2, 1.92), ("C21", "1")]),
    ("/VR_PA", SIG_W, [(46.0, 1.92), ("C20", "1")]),
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
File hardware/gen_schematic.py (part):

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                "5": "XTA", "6": None, "7": "RADIO_RST", "8": "RADIO_DIO0", "9": "RADIO_DIO1",
                "10": "RADIO_DIO2", "11": None, "12": None, "13": None, "16": "RADIO_SCK",
                "17": "RADIO_MISO", "18": "RADIO_MOSI", "19": "RADIO_NSS", "20": None,
                "25": "VR_PA", "27": None, "28": "RF_PIN", "1": "RF_RX"},
               lcsc="C67678", note="Single-path RFO_LF/RFI_LF, Semtech AN1200.19 Fig. 6, values scaled 169 -> 146 MHz"),
    "C12": c("100nF", "+3V3"),
    "C13": c("100nF", "+3V3"),
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    "C18": c("100nF", "+3V3"),
    "C19": c("10nF", "TCXO_OUT", "XTA"),
    # ---- 146 MHz match (AN1200.19 169 MHz BOM scaled by 169/146) ----
    "L1": ind("120nH", "RF_PIN", "VR_PA"),            # Lp, PA bias feed
    "C20": c("270pF", "VR_PA"),                       # Cd
    "C21": c("10nF", "VR_PA"),
    "C22": c("18pF", "RF_PIN"),                       # C1
    "C23": c("6.8pF", "RF_PIN", "RF_RX"),             # C10
    "L2": ind("91nH", "RF_RX", GND),                  # L0
    "L3": ind("68nH", "RF_PIN", "RF_A"),              # L1
    "C24": c("270pF", "RF_A", "RF_B"),                # Cc
    "C25": c("39pF", "RF_B"),                         # C2
    "L4": ind("56nH", "RF_B", "RF_C"),                # L2
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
